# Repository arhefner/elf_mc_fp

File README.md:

# elf_mc_fp
Front panel board for Lee Hart's 1802 Membership Card with Raspberry Pi interface

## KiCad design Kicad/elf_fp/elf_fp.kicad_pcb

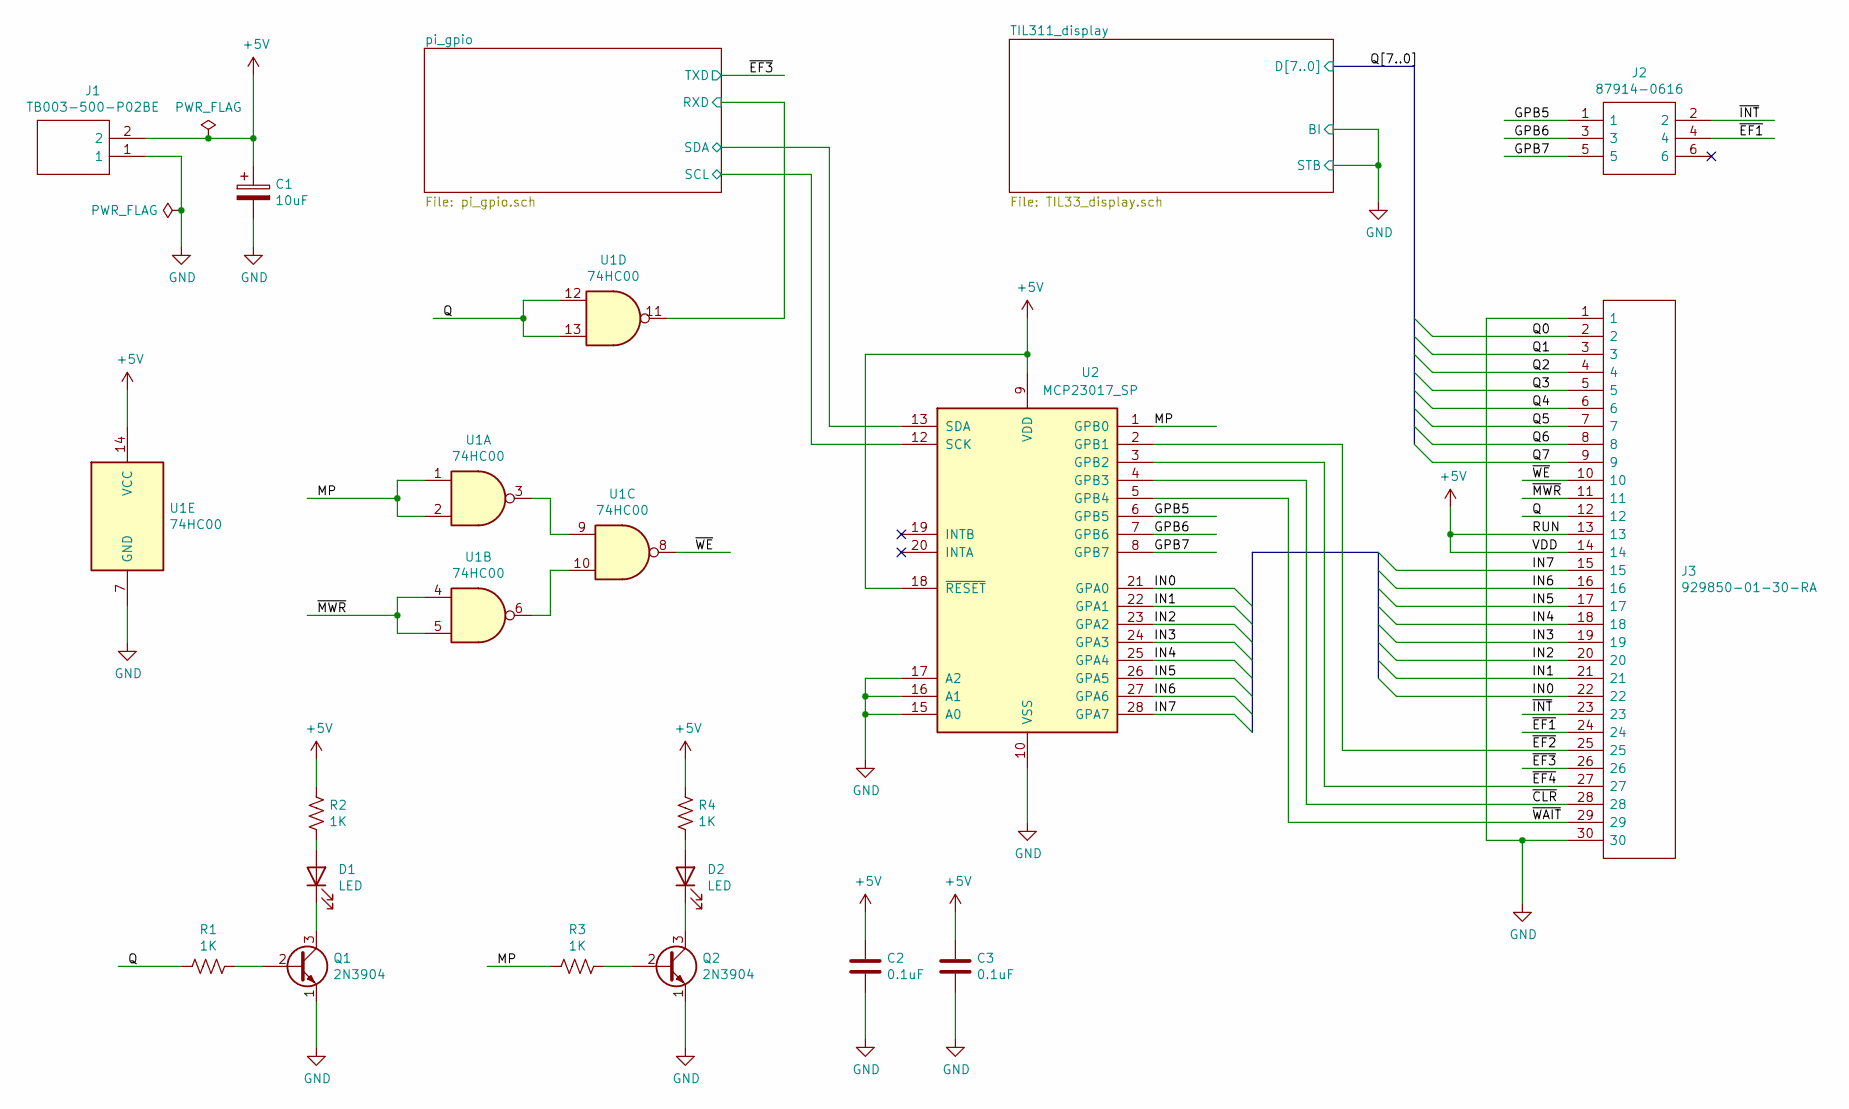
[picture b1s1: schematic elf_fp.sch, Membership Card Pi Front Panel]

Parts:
C1: 10uF; CP_Radial_Tantal_D4.5mm_P2.50mm
C2, C3: 0.1uF; C_Disc_D3.0mm_W1.6mm_P2.50mm
D1, D2: LED; LED_D3.0mm
J1: TB003-500-P02BE; SHDR2W100P0X500_1X2_1000X780X1030P; Mouser Part Number 490-TB003-500-P02BE
J2: 87914-0616; HDRV6W69P254_2X3_762X498X813P; Mouser Part Number 538-87914-0616
J3: 929850-01-30-RA; RHDR30W76P0X254_1X30_7620X254X826P; Mouser Part Number 517-929850-01-30-RA
Q1, Q2: 2N3904; TO-92_Inline
R1, R2, R3, R4: 1K; R_Axial_DIN0207_L6.3mm_D2.5mm_P7.62mm_Horizontal
U1: 74HC00; DIP-14_W7.62mm
U2: MCP23017_SP; DIP-28_W7.62mm

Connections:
+5V: C1.1, C2.1, C3.1, J1.2, J3.13, J3.14, R2.1, R4.1, U1.14 (VCC), U2.9 (VDD), U2.18 (~RESET~); also elsewhere on the board
/GPB5: J2.1, U2.6 (GPB5)
/GPB6: J2.3, U2.7 (GPB6)
/GPB7: J2.5, U2.8 (GPB7)
/IN0: J3.22, U2.21 (GPA0)
/IN1: J3.21, U2.22 (GPA1)
/IN2: J3.20, U2.23 (GPA2)
/IN3: J3.19, U2.24 (GPA3)
/IN4: J3.18, U2.25 (GPA4)
/IN5: J3.17, U2.26 (GPA5)
/IN6: J3.16, U2.27 (GPA6)
/IN7: J3.15, U2.28 (GPA7)
/MP: R3.2, U1.1, U1.2, U2.1 (GPB0)
/Q: J3.12, R1.2, U1.12, U1.13
/Q0: J3.2; also elsewhere on the board
/Q1: J3.3; also elsewhere on the board
/Q2: J3.4; also elsewhere on the board
/Q3: J3.5; also elsewhere on the board
/Q4: J3.6; also elsewhere on the board
/Q5: J3.7; also elsewhere on the board
/Q6: J3.8; also elsewhere on the board
/Q7: J3.9; also elsewhere on the board
/pi_gpio/RXD: U1.11; also elsewhere on the board
/pi_gpio/SCL: U2.12 (SCK); also elsewhere on the board
/pi_gpio/SDA: U2.13 (SDA); also elsewhere on the board
/~CLR: J3.28, U2.4 (GPB3)
/~EF1: J2.4, J3.24
/~EF2: J3.25, U2.2 (GPB1)
/~EF3: J3.26; also elsewhere on the board
/~EF4: J3.27, U2.3 (GPB2)
/~INT: J2.2, J3.23
/~MWR: J3.11, U1.4, U1.5
/~WAIT: J3.29, U2.5 (GPB4)
/~WE: J3.10, U1.8
GND: C1.2, C2.2, C3.2, J1.1, J3.1, J3.30, Q1.1 (E), Q2.1 (E), U1.7 (GND), U2.10 (VSS), U2.15 (A0), U2.16 (A1), U2.17 (A2); also elsewhere on the board
unnamed: D1.1 (K), Q1.3 (C)
unnamed: D1.2 (A), R2.2
unnamed: D2.1 (K), Q2.3 (C)
unnamed: D2.2 (A), R4.2
unnamed: Q1.2 (B), R1.1
unnamed: Q2.2 (B), R3.1
unnamed: U1.3, U1.9
unnamed: U1.6, U1.10

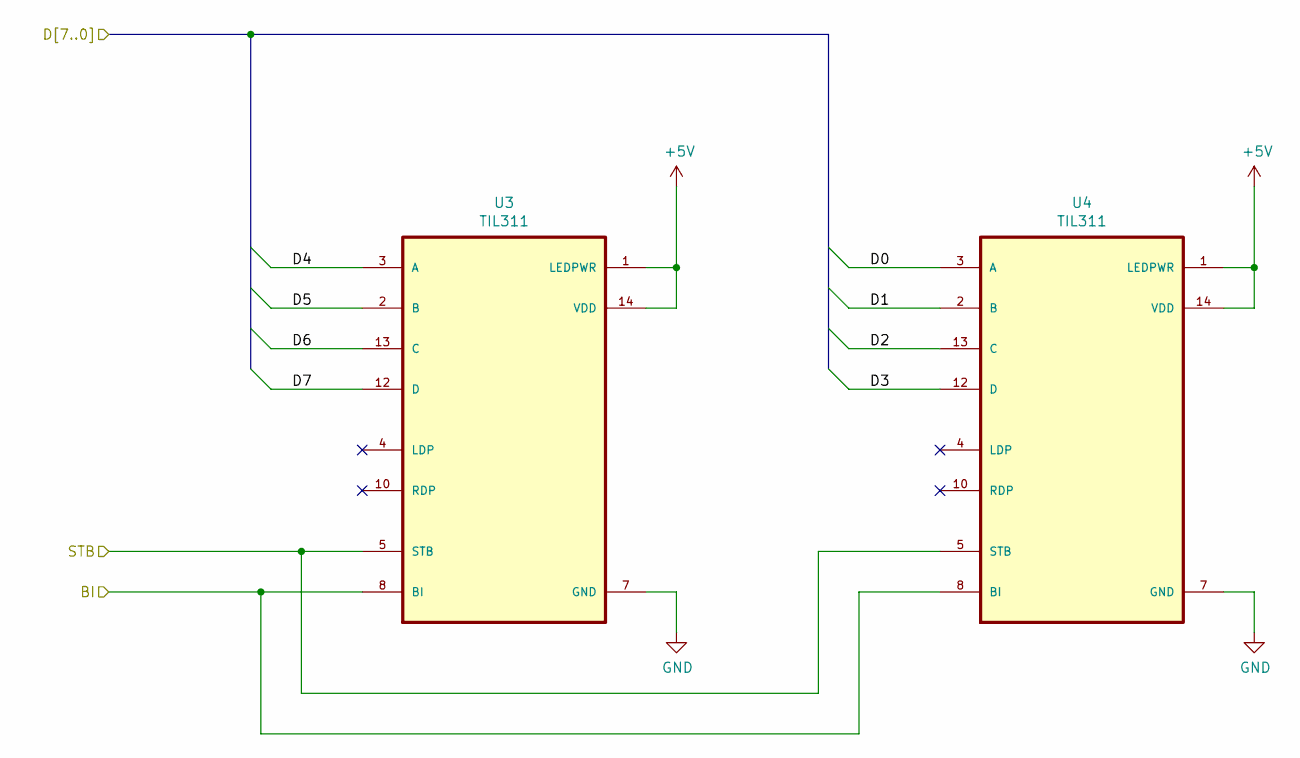
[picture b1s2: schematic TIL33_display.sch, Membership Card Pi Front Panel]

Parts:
U3, U4: TIL311; DIP794W45P254L1969H508Q14

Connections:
+5V: U3.1 (LEDPWR), U3.14 (VDD), U4.1 (LEDPWR), U4.14 (VDD); also elsewhere on the board
/Q0: U4.3 (A); also elsewhere on the board
/Q1: U4.2 (B); also elsewhere on the board
/Q2: U4.13 (C); also elsewhere on the board
/Q3: U4.12 (D); also elsewhere on the board
/Q4: U3.3 (A); also elsewhere on the board
/Q5: U3.2 (B); also elsewhere on the board
/Q6: U3.13 (C); also elsewhere on the board
/Q7: U3.12 (D); also elsewhere on the board
GND: U3.5 (STB), U3.7 (GND), U3.8 (BI), U4.5 (STB), U4.7 (GND), U4.8 (BI); also elsewhere on the board

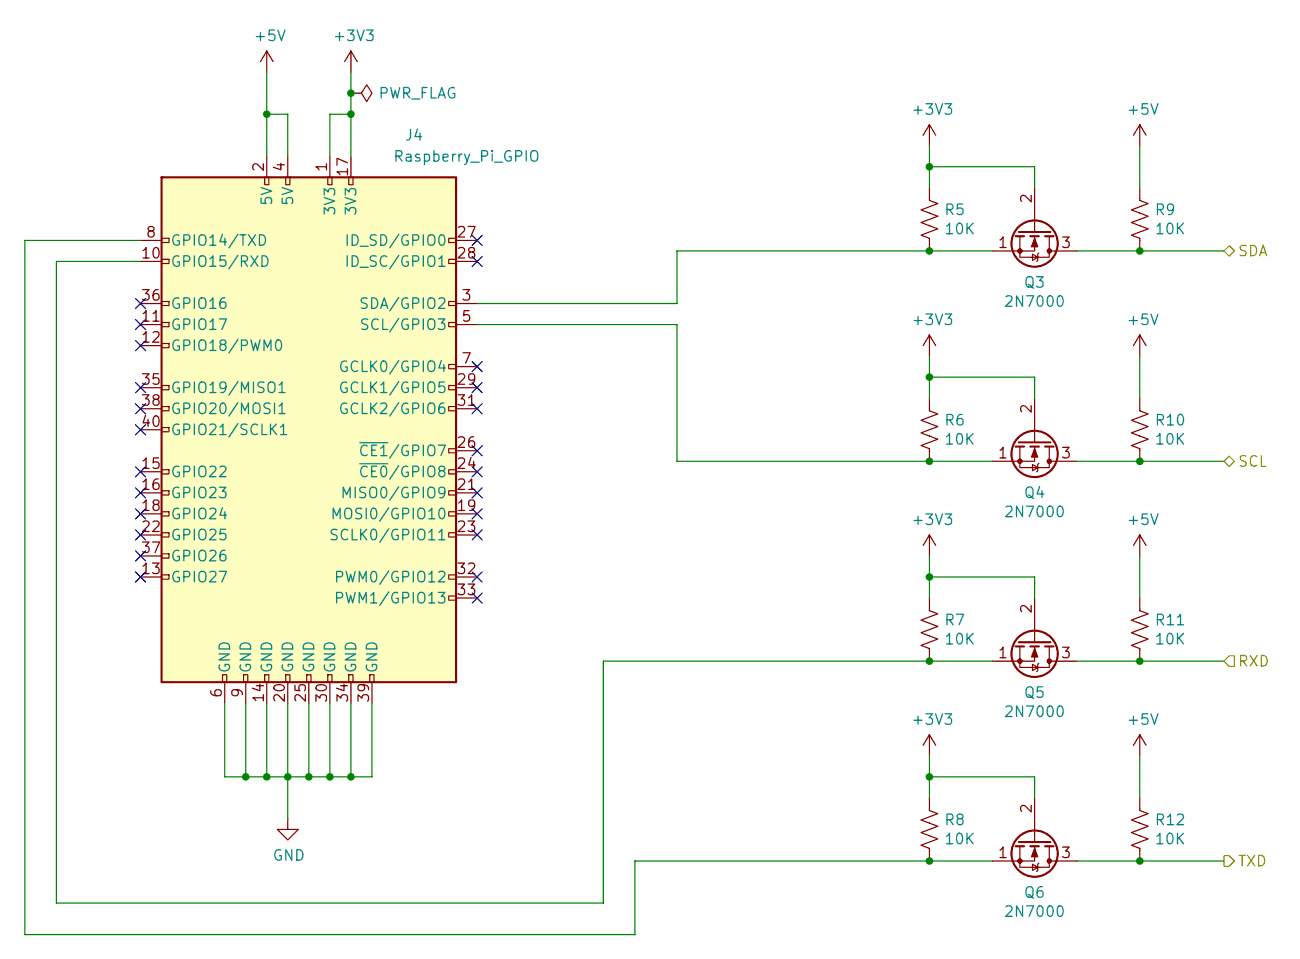
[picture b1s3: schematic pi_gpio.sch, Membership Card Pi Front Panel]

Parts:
J4: Raspberry_Pi_GPIO; SHDR40W64P254_2X20_5842X889X927P
Q3, Q4, Q5, Q6: 2N7000; TO-92_Inline
R5, R6, R7, R8, R9, R10, R11, R12: 10K; R_Axial_DIN0207_L6.3mm_D2.5mm_P7.62mm_Horizontal

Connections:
+3V3: J4.1 (3V3), J4.17 (3V3), Q3.2 (G), Q4.2 (G), Q5.2 (G), Q6.2 (G), R5.1, R6.1, R7.1, R8.1
+5V: J4.2 (5V), J4.4 (5V), R9.1, R10.1, R11.1, R12.1; also elsewhere on the board
/pi_gpio/RXD: Q5.3 (D), R11.2; also elsewhere on the board
/pi_gpio/SCL: Q4.3 (D), R10.2; also elsewhere on the board
/pi_gpio/SDA: Q3.3 (D), R9.2; also elsewhere on the board
/~EF3: Q6.3 (D), R12.2; also elsewhere on the board
GND: J4.6 (GND), J4.9 (GND), J4.14 (GND), J4.20 (GND), J4.25 (GND), J4.30 (GND), J4.34 (GND), J4.39 (GND); also elsewhere on the board
unnamed: J4.3 (SDA/GPIO2), Q3.1 (S), R5.2
unnamed: J4.5 (SCL/GPIO3), Q4.1 (S), R6.2
unnamed: J4.8 (GPIO14/TXD), Q6.1 (S), R8.2
unnamed: J4.10 (GPIO15/RXD), Q5.1 (S), R7.2

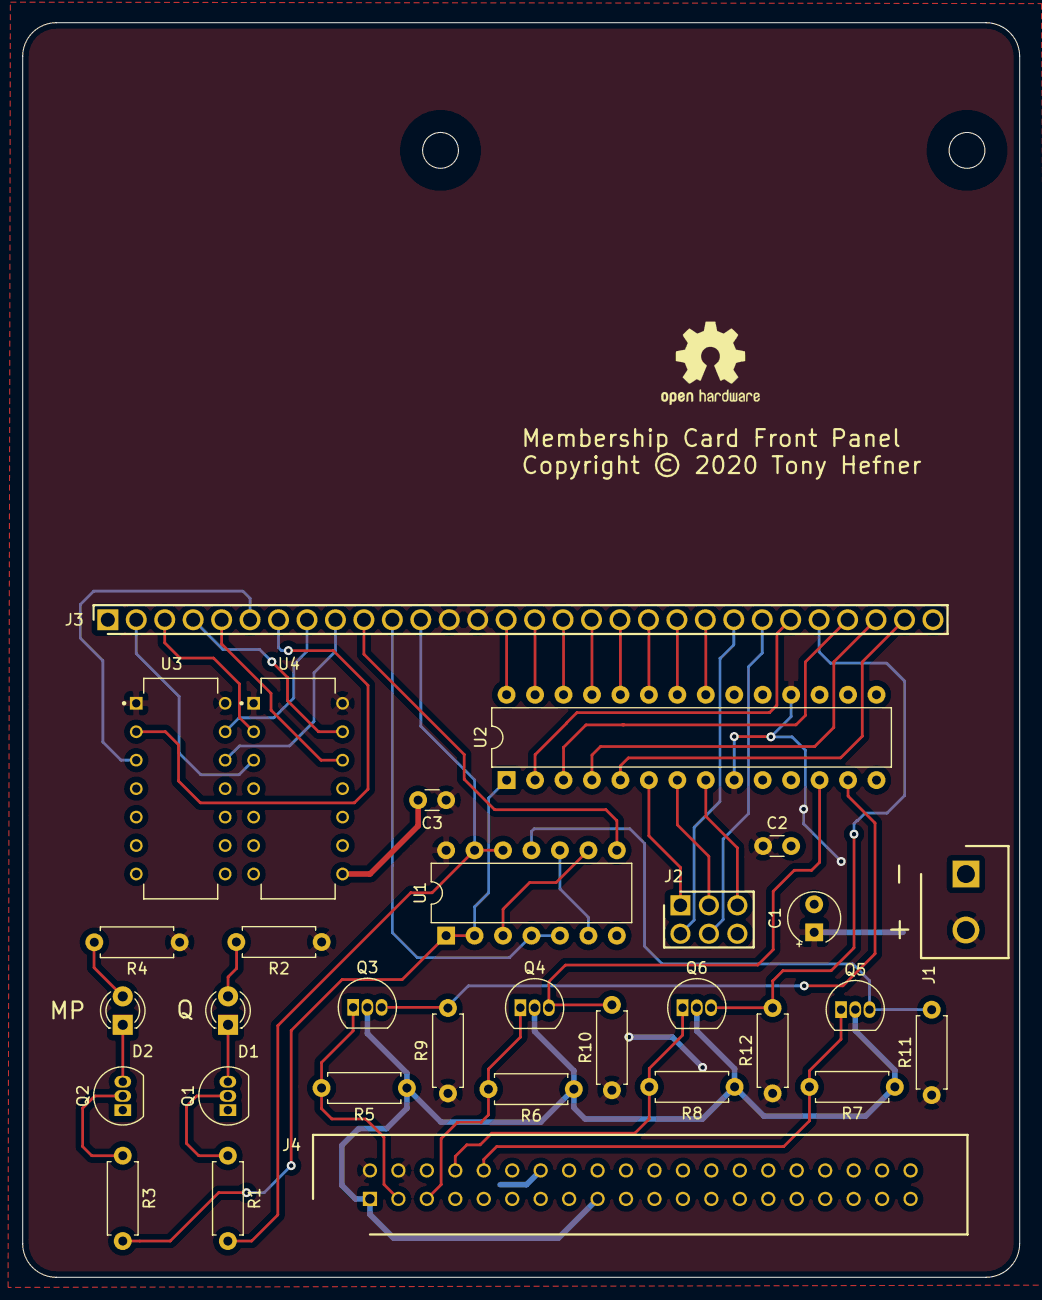
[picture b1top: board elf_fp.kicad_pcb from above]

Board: 2 copper layers, 89.0 x 112.0 mm, 31 parts (0 on the bottom side), 48 nets.

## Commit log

2021-02-07 Add KiCad schematic/pcb.
2021-02-07 Add pdf schematic.
2021-02-07 Add python scripts for driving front panel.

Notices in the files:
Kicad/elf_fp/elf_fp.kicad_pcb:
Copyright © 2020 Tony Hefner
